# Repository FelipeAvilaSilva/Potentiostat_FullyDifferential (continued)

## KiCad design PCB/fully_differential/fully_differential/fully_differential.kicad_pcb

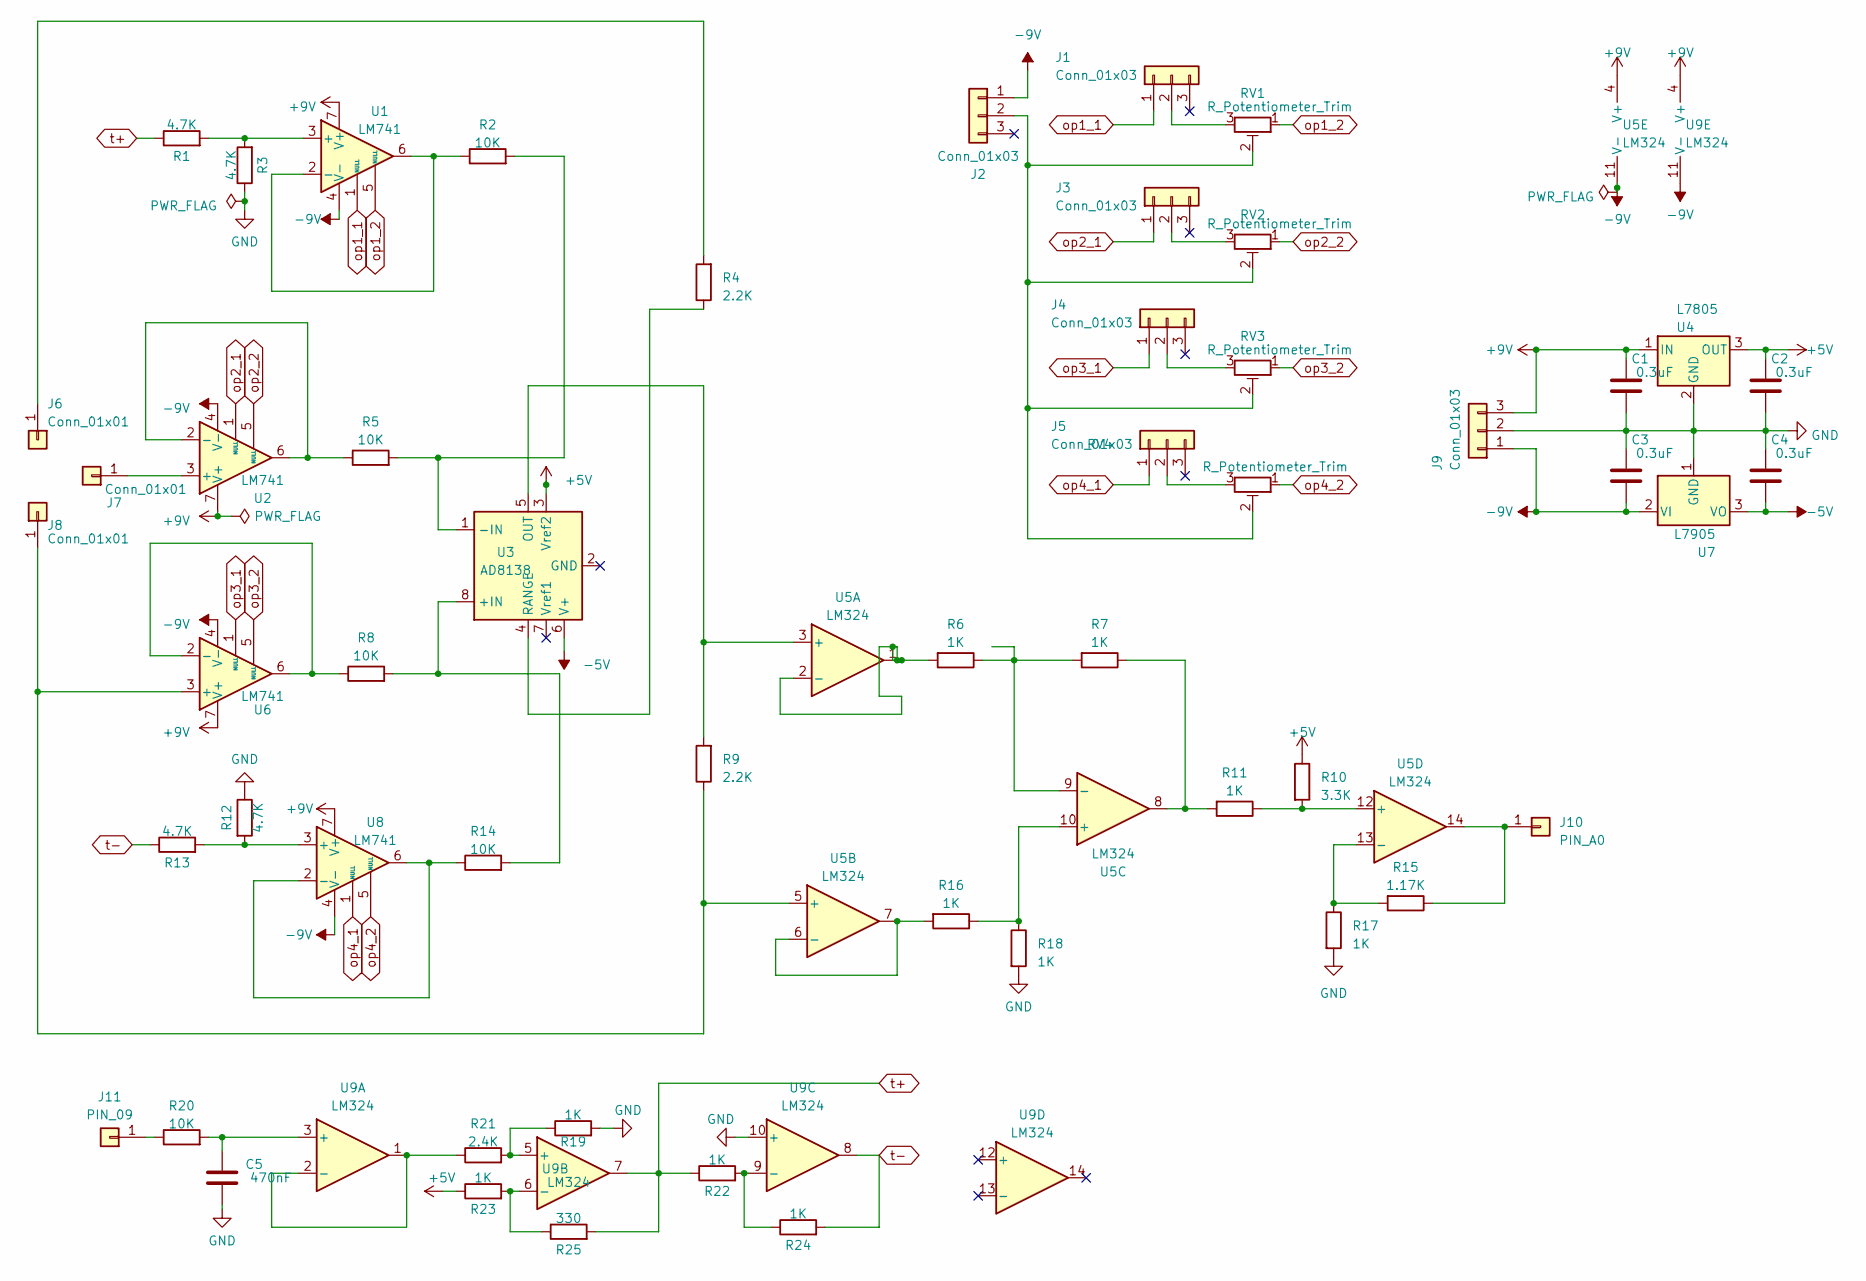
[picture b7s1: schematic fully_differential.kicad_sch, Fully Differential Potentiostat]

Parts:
C1, C2, C3, C4: 0.3uF; CP_Radial_D5.0mm_P2.00mm
C5: 470nF; C_Rect_L19.0mm_W6.0mm_P15.00mm_MKS4
J1, J2, J3, J4, J5: Conn_01x03; PinHeader_1x03_P2.54mm_Vertical
J6, J7, J8: Conn_01x01; PinHeader_1x01_P2.54mm_Vertical
J9: Conn_01x03; Stocko_MKS_1653-6-0-303_1x3_P2.50mm_Vertical
J10: PIN_A0; PinHeader_1x01_P2.54mm_Vertical
J11: PIN_09; PinHeader_1x01_P2.54mm_Vertical
R1, R3, R12, R13: 4.7K; R_Axial_DIN0207_L6.3mm_D2.5mm_P10.16mm_Horizontal
R2, R5, R8, R14, R20: 10K; R_Axial_DIN0207_L6.3mm_D2.5mm_P10.16mm_Horizontal
R4, R9: 2.2K; R_Axial_DIN0207_L6.3mm_D2.5mm_P10.16mm_Horizontal
R6, R7, R11, R16, R17, R18, R19, R22, R23, R24: 1K; R_Axial_DIN0207_L6.3mm_D2.5mm_P10.16mm_Horizontal
R10: 3.3K; R_Axial_DIN0207_L6.3mm_D2.5mm_P10.16mm_Horizontal
R15: 1.17K; R_Axial_DIN0207_L6.3mm_D2.5mm_P10.16mm_Horizontal
R21: 2.4K; R_Axial_DIN0207_L6.3mm_D2.5mm_P10.16mm_Horizontal
R25: 330; R_Axial_DIN0207_L6.3mm_D2.5mm_P10.16mm_Horizontal
RV1, RV2, RV3, RV4: R_Potentiometer_Trim; Potentiometer_Bourns_3296W_Vertical
U1, U2, U6, U8: LM741; DIP794W45P254L959H508Q8
U3: AD8138; SOIC-8_3.9x4.9mm_P1.27mm
U4: L7805; TO255P1020X450X2000-3
U5, U9: LM324; DIP825W47P254L1917H533Q14
U7: L7905; TO255P1020X450X2000-3

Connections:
+5V: C2.1, R10.1, R23.1, U3.3 (Vref2), U4.3 (OUT)
+9V: C1.1, J9.3, U1.7 (V+), U2.7 (V+), U4.1 (IN), U5.4 (V+), U6.7 (V+), U8.7 (V+), U9.4 (V+)
-5V: C4.2, U3.6 (V+), U7.3 (VO)
-9V: C3.2, J2.1, J9.1, U1.4 (V-), U2.4 (V-), U5.11 (V-), U6.4 (V-), U7.2 (VI), U8.4 (V-), U9.11 (V-)
GND: C1.2, C2.2, C3.1, C4.1, C5.2, J9.2, R3.1, R12.1, R17.2, R18.2, R19.2, U4.2 (GND), U7.1 (GND), U9.10 (+)
unnamed: J1.2, RV1.3
unnamed: J2.2, RV1.2, RV2.2, RV3.2, RV4.2
unnamed: J3.2, RV2.3
unnamed: J4.2, RV3.3
unnamed: J5.2, RV4.3
unnamed: J6.1, R4.2
unnamed: J7.1, U2.3 (+)
unnamed: J8.1, R9.1, U5.5 (+), U6.3 (+)
unnamed: J10.1, R15.1, U5.14
unnamed: J11.1, R20.1
unnamed: R7.1, R11.2, U5.8
unnamed: R1.2, R3.2, U1.3 (+)
unnamed: R2.1, U1.2 (-), U1.6
unnamed: R5.1, U2.2 (-), U2.6
unnamed: R8.2, R14.2, U3.8 (+IN)
unnamed: R2.2, R5.2, U3.1 (-IN)
unnamed: R9.2, U3.5 (OUT), U5.3 (+)
unnamed: R4.1, U3.4 (RANGE)
unnamed: R6.2, U5.1, U5.2 (-)
unnamed: R16.2, U5.6 (-), U5.7
unnamed: R16.1, R18.1, U5.10 (+)
unnamed: R6.1, R7.2, U5.9 (-)
unnamed: R10.2, R11.1, U5.12 (+)
unnamed: R15.2, R17.1, U5.13 (-)
unnamed: R8.1, U6.2 (-), U6.6
unnamed: R12.2, R13.2, U8.3 (+)
unnamed: R14.1, U8.2 (-), U8.6
unnamed: C5.1, R20.2, U9.3 (+)
unnamed: R21.1, U9.1, U9.2 (-)
unnamed: R19.1, R21.2, U9.5 (+)
unnamed: R23.2, R25.1, U9.6 (-)
unnamed: R22.2, R24.1, U9.9 (-)
op1_1: J1.1, U1.1 (NULL)
op1_2: RV1.1, U1.5 (NULL)
op2_1: J3.1, U2.1 (NULL)
op2_2: RV2.1, U2.5 (NULL)
op3_1: J4.1, U6.1 (NULL)
op3_2: RV3.1, U6.5 (NULL)
op4_1: J5.1, U8.1 (NULL)
op4_2: RV4.1, U8.5 (NULL)
t+: R1.1, R22.1, R25.2, U9.7
t-: R13.1, R24.2, U9.8

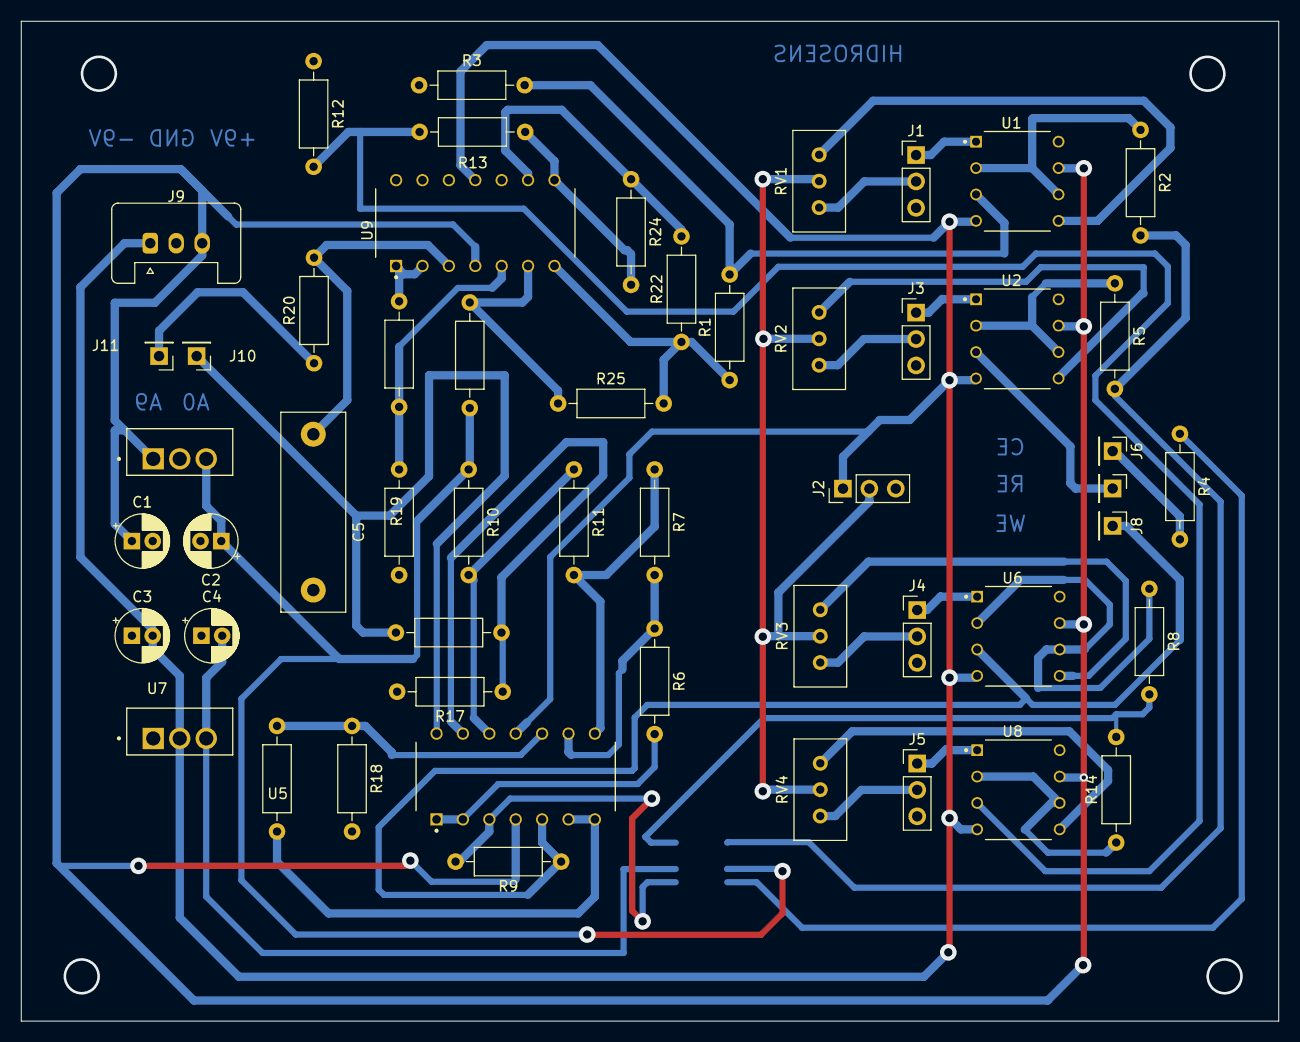
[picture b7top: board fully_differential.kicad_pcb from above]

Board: 2 copper layers, 121.0 x 96.2 mm, 54 parts (1 on the bottom side), 47 nets.

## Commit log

2022-11-22 init
    ISIS PROFESSIONAL
2022-11-22 fix
    falta vcell
2022-11-22 day ok
2023-02-09 add mod in 3 poten
2023-02-13 att ampop corrente/tensão
2023-02-16 add ino
2023-02-24 read arduino serial port with python
2023-02-24 graph python
2023-02-28 add graph
    clear folder
    add txt
    fix signal single&fully
2023-02-28 add 2 cores in graph
2023-02-28 add graph
2023-03-07 add def writetxt
2023-03-07 upgrade graph and input serial
2023-03-14 add scan, start, end
    in python
    calibration
2023-03-29 test fully, add img, fix ino
2023-04-24 fix fully
    fix ler dados, calibração, pwm, buffer, ad8138
2023-04-25 fix pcb paste
2023-05-05 v1 pcb
    add basic, vcc-gnd
2023-05-22 new pcb
    falta validar para impressao
2023-05-26 pcb finalizado
    falta retirar divisor de tensao e mudar a leitura da tensao no resistor superior
2023-06-19 add v4
    versao da segunda impressão na cnc
2023-07-04 fix proteus 1.5v and 3v
    stock v2 proteus and kicad ok
    fully v4 proteus and kicad ok
2023-07-21 att read serial for notebook
2023-08-18 tudo ok
    se e fd pcb ok
2023-08-23 Git for test lab
    Andar 1
2023-10-25 Clean Code
    Clean Code in funtion voltametry cyclic
    SerialPython3 fix, delay, name.txt
2023-10-25 Clean Code
2023-10-31 FIX tree function
2023-11-06 graph fix
2023-11-10 att
    melhorei definição de sobreamostragem, intervals delay, analogreference, velocidade serial
2023-11-10 fix scan rate
    att
2023-11-29 Att
    Troquei resistor r3 de 10k por 1k, adicionei filtro no python, eliminei os 10 primeiros pontos do grafico
2023-11-29 att
    agora funciona varredura de -1v a 1v no proteus
2023-12-05 Update
    Ultimo teste 2023
2023-12-06 Att
    add funcao 0 para teste, correção sentido do grafico de preview
2023-12-06 fix
    correção do zero bugado entre as medidas
2023-12-14 Teste Prototipo
2024-01-31 Version SMD
    Init pcb, lib
2024-01-31 schamatic
    init
